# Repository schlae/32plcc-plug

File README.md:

# 32-pin PLCC Plug and Interposer

Ever need to probe the address and data lines of a ROM chip while it is connected in another circuit board? Or maybe you want to build a board to emulate a ROM chip using a microcontroller or something. Here's a solution: a 3D-printable 32-pin PLCC plug that can be paired up with an optional interposer circuit board.

Some of the compatible ROM chips include:

- 27C256
- 27C512
- 27C010
- 48F010
- 27C020
- 39VF010

## The plug

The plug body can easily be printed with a standard FDM printer. I use an Ender 3 with the detail set to low.

After the print, you may need to clear out the holes and widen them slightly with a pushpin. They are sized so that square pins from a 0.1" header will fit into them. If you salvage the pins from a right angle header, you won't even need to worry about bending them.

Be very careful when soldering the plug since the plastic melts very easily. Use a lower temperature setting on your soldering iron, and consider using a low melting point solder such as Chip Quik.

[Plug STL file](https://github.com/schlae/32plcc-plug/blob/main/32plccplug1.STL)

## The interposer board

One way to use this plug is to solder it to an interposer board which makes it easy to probe pin connections with a ROM chip connected in a pass-through arrangement. Of course, you can use it for whatever you want, borrowing the footprint from the interposer board design.

The headers around the edges of the board are designed for standard 0.1" header pins which can be connected to logic analyzer probes.

## License

This work is licensed under a Creative Commons Attribution-ShareAlike 4.0
International License. See [https://creativecommons.org/licenses/by-sa/4.0/](https://creativecommons.org/licenses/by-sa/4.0/).

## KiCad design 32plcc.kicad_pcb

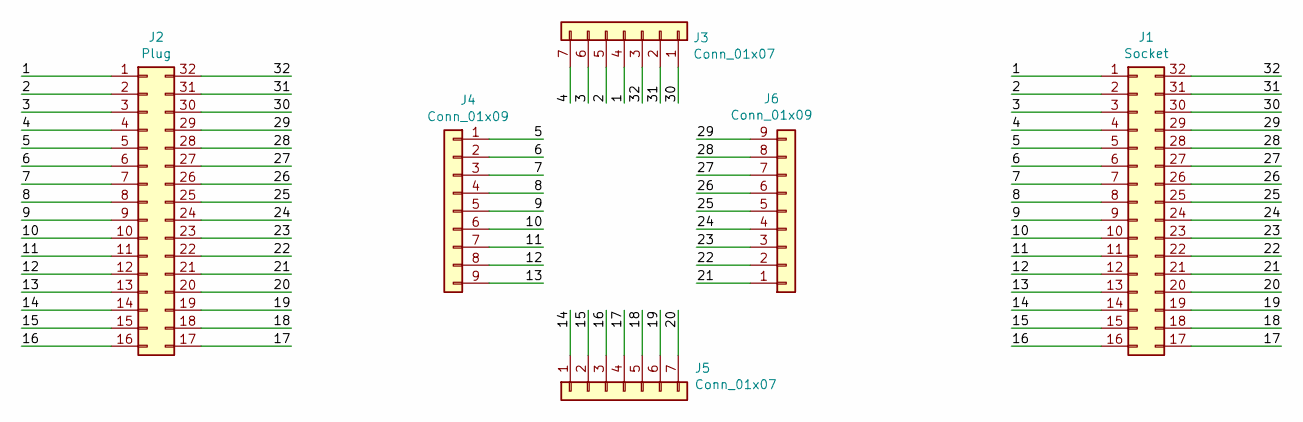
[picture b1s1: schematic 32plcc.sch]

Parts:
J1: Socket; PLCCS127P1250X1500X370-32
J2: Plug; PLCCP127P1250X1500X370-32
J3, J5: Conn_01x07; Pin_Header_Straight_1x07_Pitch2.54mm
J4, J6: Conn_01x09; Pin_Header_Straight_1x09_Pitch2.54mm

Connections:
/1: J1.1, J2.1, J3.4
/2: J1.2, J2.2, J3.5
/3: J1.3, J2.3, J3.6
/4: J1.4, J2.4, J3.7
/5: J1.5, J2.5, J4.1
/6: J1.6, J2.6, J4.2
/7: J1.7, J2.7, J4.3
/8: J1.8, J2.8, J4.4
/9: J1.9, J2.9, J4.5
/10: J1.10, J2.10, J4.6
/11: J1.11, J2.11, J4.7
/12: J1.12, J2.12, J4.8
/13: J1.13, J2.13, J4.9
/14: J1.14, J2.14, J5.1
/15: J1.15, J2.15, J5.2
/16: J1.16, J2.16, J5.3
/17: J1.17, J2.17, J5.4
/18: J1.18, J2.18, J5.5
/19: J1.19, J2.19, J5.6
/20: J1.20, J2.20, J5.7
/21: J1.21, J2.21, J6.1
/22: J1.22, J2.22, J6.2
/23: J1.23, J2.23, J6.3
/24: J1.24, J2.24, J6.4
/25: J1.25, J2.25, J6.5
/26: J1.26, J2.26, J6.6
/27: J1.27, J2.27, J6.7
/28: J1.28, J2.28, J6.8
/29: J1.29, J2.29, J6.9
/30: J1.30, J2.30, J3.1
/31: J1.31, J2.31, J3.2
/32: J1.32, J2.32, J3.3

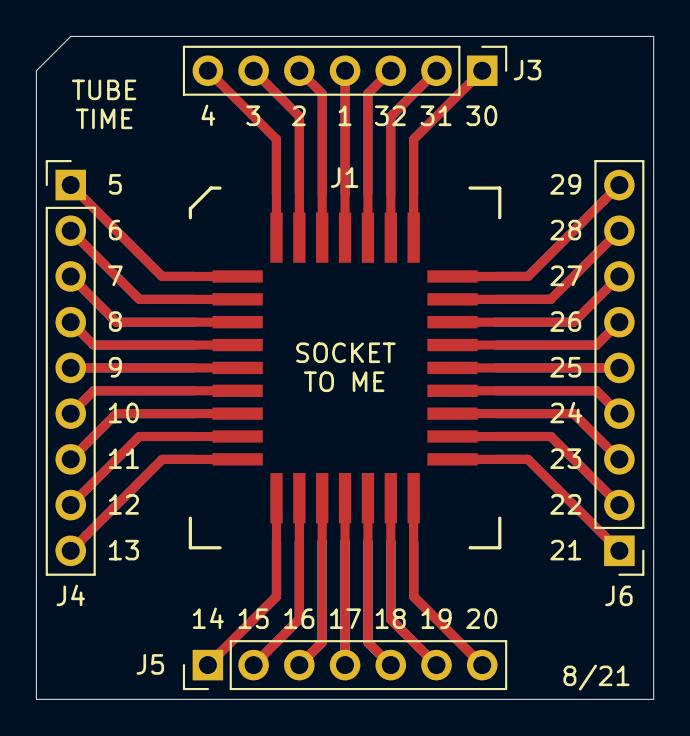
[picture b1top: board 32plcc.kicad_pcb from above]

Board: 2 copper layers, 34.3 x 36.8 mm, 6 parts (1 on the bottom side), 32 nets.

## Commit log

2021-11-11 initial empty commit
2021-11-11 Add license info
